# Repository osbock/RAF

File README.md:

# RAF - Ready...Aim...Fire!
Software for a beginning programming class with Arduino, and IOT programming with MQTT. Hardware consists of an Arduino, Shield, Pan/tilt mechanism and pneumatic components for firing foam darts

## Instructions
 * [Assembly Instructions](./Documents/Assembly.md)
 * [Software setup](./Documents/Software.md)

## Software requirements
 * Arduino IDE
 * Python 3.X
 * Adafruit IOT python package

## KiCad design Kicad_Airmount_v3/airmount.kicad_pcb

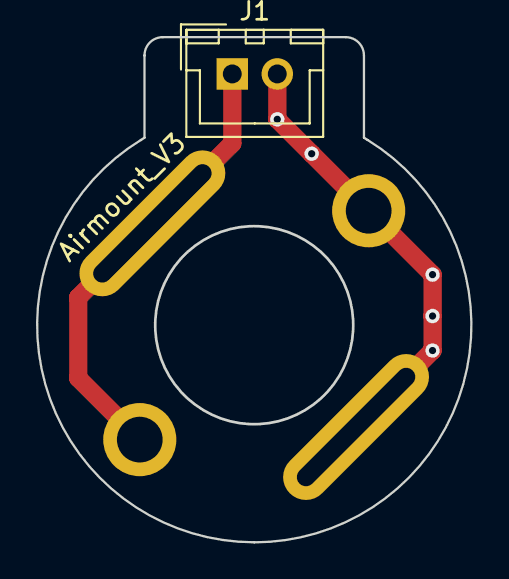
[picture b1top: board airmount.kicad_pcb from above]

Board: 2 copper layers, 24.1 x 28.0 mm, 4 parts (0 on the bottom side), 2 nets.

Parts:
Board1: pumpBoard2
J1: JST; JST_XH_B02B-XH-A_02x2.50mm_Straight
M1: Motor_DC; p_contacts2
M2: Motor_DC; GasSolenoid2

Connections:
GND: J1.2, M1.2, M2.2
unnamed: J1.1, M1.1, M2.1

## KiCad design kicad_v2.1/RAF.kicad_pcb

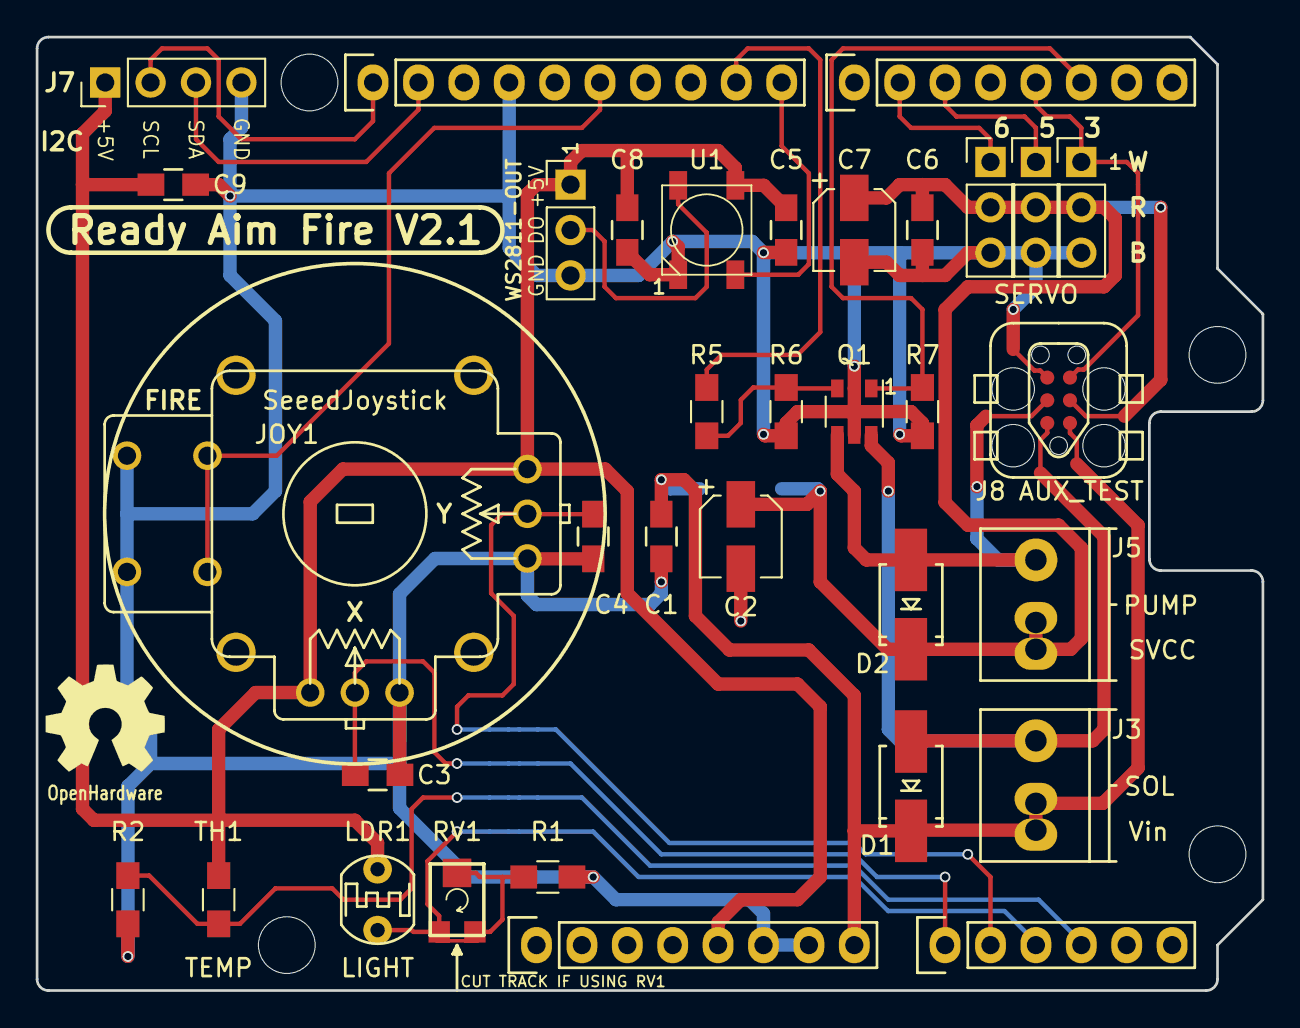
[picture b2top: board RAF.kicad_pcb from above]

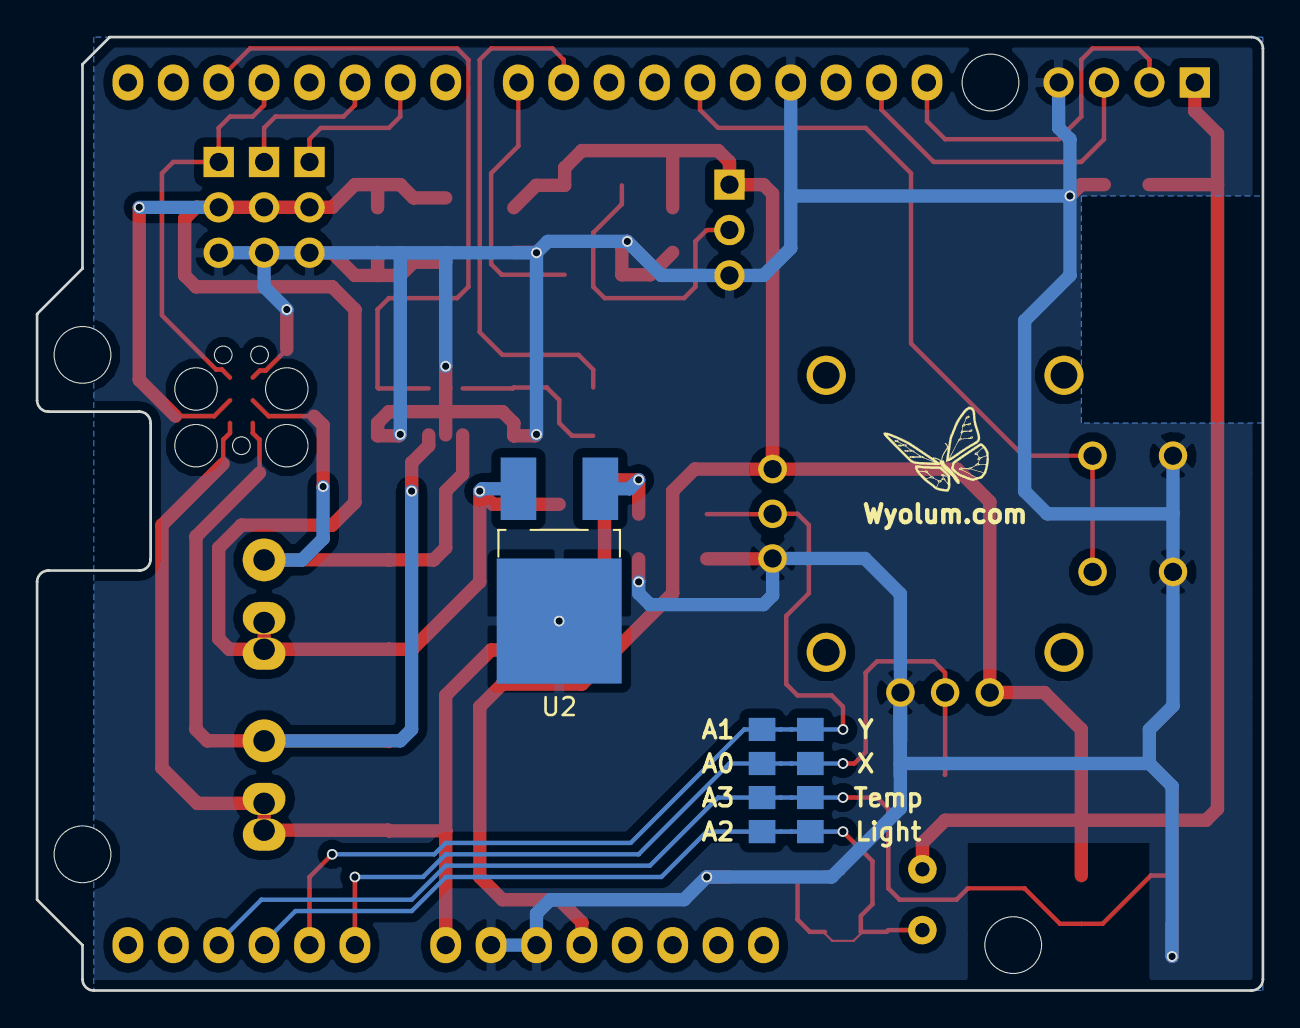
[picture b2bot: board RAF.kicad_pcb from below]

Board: 2 copper layers, 68.6 x 53.3 mm, 45 parts (6 on the bottom side), 21 nets.

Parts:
C1, C3, C4, C5, C6, C8, C9: 0.1uF; C_0805_HandSoldering
C2, C7: 22uF; CP_Elec_4x5.7
D1, D2: S1ATR; SMA_Handsoldering
H1, H2, H3, H4: NPTH_hole; NPTH_hole_3mm
J1, J2, J4: SERVO; Pin_Header_Straight_1x03_Pitch2.54mm
J3: SOL; TerminalBlock_Pheonix_PT-5.0mm_2pol
J5: PUMP; TerminalBlock_Pheonix_PT-5.0mm_2pol
J6: WS2811-OUT; Pin_Header_Straight_1x03_Pitch2.54mm
J7: I2C; Pin_Header_Straight_1x04_Pitch2.54mm
J8: AUX_TEST; TC2030-IDC
JOY1: SeeedJoystick; SEEED-Joystick_v2
JP1, JP2, JP3, JP4: Jumper_NC_Small; 0805_jumper
LDR1: LIGHT; Resistor_LDR_5.0x3.4
OSHW1: OSHW; OSHW_6mm
P1: Power; Socket_Strip_Arduino_1x08
P2: Analog; Socket_Strip_Arduino_1x06
P3: Digital; Socket_Strip_Arduino_1x10
P4: Digital; Socket_Strip_Arduino_1x08
Q1: FDC6305N; SuperSOT-6
R1: 22K; R_0805_HandSoldering
R2: 10K; R_0805_HandSoldering
R5, R6, R7: 100k; R_0805_HandSoldering
RV1: 100k; Res_variable
TH1: TEMP; R_0805_HandSoldering
U1: RGB_WS2811B; LED_WS2812B-PLCC4
U2: LF60CDT; DPak
WYO1: LOGO_WL; logo_wyo_butterfly_small

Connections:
+5V: C5.1, C8.1, C9.1, J6.1, J7.1, JOY1.X+, JOY1.Y+, LDR1.1, P1.5, TH1.1, U1.1
/2: P4.6, Q1.1, R7.2
/3(**): J1.1, J8.5, P4.5
/5(**): J2.1, P4.3
/6(**): J4.1, P4.2
/8: P3.10, U1.4
/9(**): P3.9, R5.2
/12(MISO): JOY1.B1, JOY1.B2, P3.6
/A0: C3.1, JOY1.X, JP1.1, JP1.2, P2.1
/A1: C4.1, JOY1.Y, JP2.1, JP2.2, P2.2
/A2: JP3.1, JP3.2, LDR1.2, P2.3, R1.1, RV1.1, RV1.2, RV1.3
/A3: JP4.1, JP4.2, P2.4, R2.1, TH1.2
/A4(SDA): J7.3, P3.2
/A5(SCL): J7.2, P3.1
/LED_OUT: J6.2, U1.2
/PUMP: D2.2, J5.2, J8.4, Q1.4
/SOL: D1.2, J3.2, J8.2, Q1.6
/SVCC: C2.1, C6.1, C7.1, D2.1, J1.2, J2.2, J4.2, J5.1, J8.3, U2.VO
/Vin: C1.1, D1.1, J3.1, J8.1, P1.8, U2.VI
GND: C1.2, C2.2, C3.2, C4.2, C5.2, C6.2, C7.2, C8.2, C9.2, J1.3, J2.3, J4.3, J6.3, J7.4, J8.6, JOY1.A1, JOY1.A2, JOY1.X-, JOY1.Y-, P1.6, P1.7, P3.4, Q1.2, Q1.5, R1.2, R2.2, R6.1, R7.1, U1.3, U2.GND
unnamed: Q1.3, R5.1, R6.2

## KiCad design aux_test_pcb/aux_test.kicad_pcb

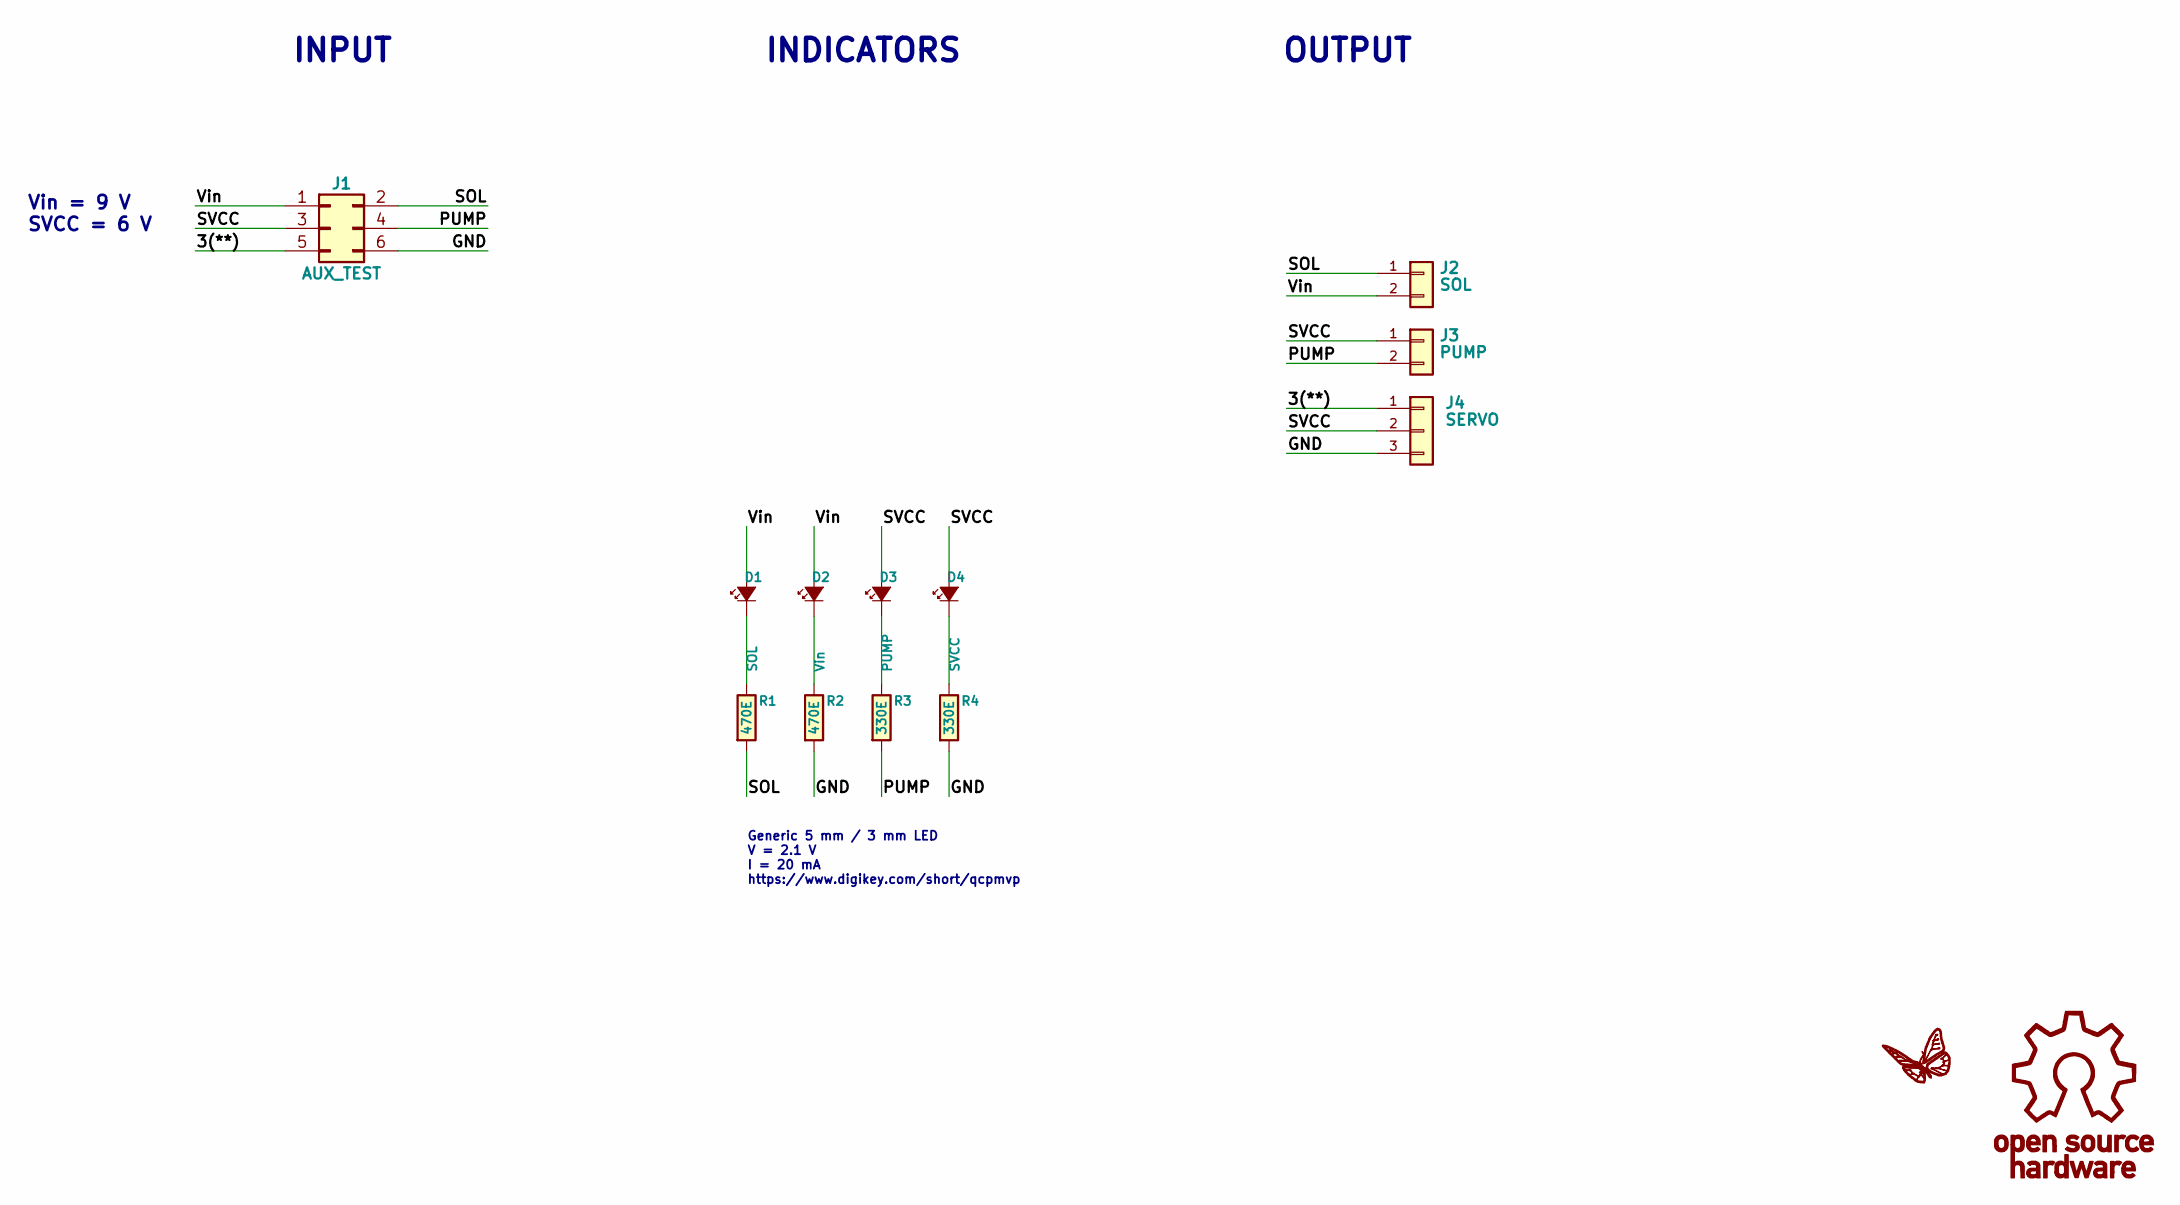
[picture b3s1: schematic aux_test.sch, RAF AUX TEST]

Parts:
D1: SOL; LED-5MM
D2: Vin; LED-5MM
D3: PUMP; LED-5MM
D4: SVCC; LED-5MM
J1: AUX_TEST; Pin_Header_Straight_2x03
J2: SOL; TerminalBlock_Pheonix_PT-5.0mm_2pol
J3: PUMP; TerminalBlock_Pheonix_PT-5.0mm_2pol
J4: SERVO; Pin_Header_Straight_1x03_Pitch2.54mm
R1, R2: 470E; Resistor_Horizontal_RM10mm
R3, R4: 330E; Resistor_Horizontal_RM10mm

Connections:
/3(**): J1.5, J4.1
/GND: J1.6, J4.3, R2.2, R4.2
/PUMP: J1.4, J3.2, R3.2
/SOL: J1.2, J2.1, R1.2
/SVCC: D3.1 (A), D4.1 (A), J1.3, J3.1, J4.2
/Vin: D1.1 (A), D2.1 (A), J1.1, J2.2
unnamed: D1.2 (K), R1.1
unnamed: D2.2 (K), R2.1
unnamed: D3.2 (K), R3.1
unnamed: D4.2 (K), R4.1

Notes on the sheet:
Generic 5 mm / 3 mm LED V = 2.1 V I = 20 mA https://www.digikey.com/short/qcpmvp
INPUT
INDICATORS
OUTPUT
Vin = 9 V SVCC = 6 V

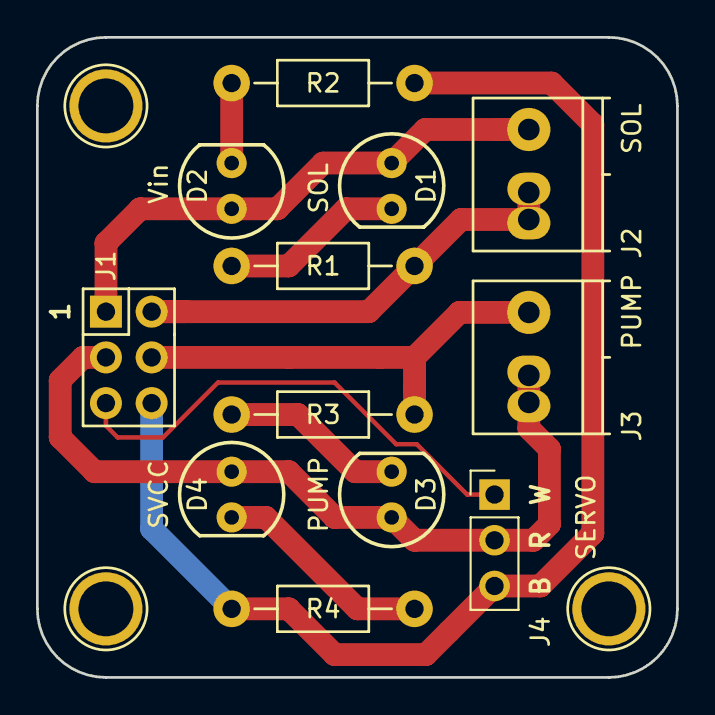
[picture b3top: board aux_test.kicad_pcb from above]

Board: 2 copper layers, 35.6 x 35.6 mm, 15 parts (0 on the bottom side), 10 nets.

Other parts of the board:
1pin, 1pin#2, 1pin#3: VAL**; hole_3mm

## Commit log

2017-05-15 Add arduino code
2017-05-15 add readme
2017-05-15 add documentation
2017-05-15 start python mqtt proxy
2017-05-16 add serial version, adjust servo senters for new pantilt
2017-05-16 update for azimuth/elevation and fire feeds:
2017-05-17 add software setup instructions
2017-05-17 cross link software in README
2017-05-17 fix header
2017-05-17 add fire command to rafserial
2017-05-17 fix fire func in rafserial, limits
2017-05-19 add mounting plate
2017-05-22 add legs, move holes around a bit
2017-07-07 new cloud service [wip]
2017-07-13 update servo positions
2017-07-13 servo align sketch for pan tilt assembly
2017-07-24 initial commit, kicad version Ready Aim Fire Shield V2
2017-07-25 mostly finished schematic
2017-07-25 add sot23-6 footprint, fix drc errors
2017-07-25 add i2c header
2017-07-25 update footprint allocation
2017-08-01 new parts, initial layout, backup of switcher design
2017-08-02 layout and gerbers
2017-08-09 add RAF2 Example
2017-08-09 add pin 1 indications for LED and mosfet
2017-08-09 add FastLED copy, update RAF2 example
2017-08-11 add FastLED support
2017-08-22 add seeed bom
2017-08-23 updated do not populate
2017-08-23 add labels for the mosfet terminals
2017-08-24 HW ver2 of kicad
2017-08-24 RAF v3 Kicad WIP
2017-08-25 add pcb spec file for Seeed
2017-08-25 RAF v2.1 kicad layout
2017-08-25 folder rename
2017-08-25 update bom for cds and datasheet
2017-08-25 LDR footprint modified
2017-08-25 removed kicad_v2 folder
2017-08-26 PCB ver2.1 complete, added variable resistor for LDR
2017-08-26 kicad_v2.1 updated silkscreen
2017-08-26 added FreeCad and step models of PCB to fabricate folder
2017-09-05 add seeed joystick info
2017-09-05 seeed joystick revision
2017-09-05 joystick 3D updated
2017-09-05 updated 3D model in fabricate
2017-09-06 added pogo connector for testing solenoid, pump, servo
2017-09-06 cleaned up silk legend
2017-09-07 aux_text board for production testing
2017-09-08 aux_test minor mods
2017-09-18 fix C2 and C7 value, update to 5mm screw terminals
2017-09-20 pin 1 markers added on silk legend
2017-09-20 updated images
2017-09-21 fix servo legend
2017-09-21 fixed errors in aux_test layout
2017-09-22 updated aux_test PCB
2017-09-22 added aux_test gerber
2017-09-22 refine RAFTest to manufacturing test
2017-10-02 update bom with links
2017-10-03 modified screw terminal solder pads
2017-10-06 remove tactile switch
2017-10-09 edited values of C2,C7
2017-10-12 cleanup
2017-12-15 update for new pan/tilt
2017-12-20 add missing 3d printed pieces
2017-12-22 add assembly v2 images
2017-12-22 update for v2 and air pump
2018-01-02 update content image
2018-01-02 rotate some images:
2018-01-02 New V2 assembly instructions (incomplete)
2018-01-02 finished through Pneumatic assembly.
2018-01-02 rotate another image
2018-01-02 incremental update to assembly instructions
2018-01-02 Link in assembly instrcutions
2018-01-02 and done with Assembly.md
2018-01-02 crop overview pic
2018-01-03 add formatted assembly instructions
2018-01-09 update bom
2018-04-20 add note about python on macs
2018-04-20 refresh install changes, remove stale downloads
2018-04-20 add ada.io section
2018-05-22 servo-step1
2018-05-22 update raf2 for new servos
2018-06-06 add barrelholder, update solenoid holder
2018-07-27 add airmount pcb
2018-07-28 Airmount _v2 and _v3
2018-07-28 Airmount _v2 and _v3 revised gerbers
2019-04-14 Add slew-not-absolute version
2019-04-14 Autoformat
2019-04-14 remove old RAF code
2019-05-14 Make python setup optional/warning about accuracy
2019-07-22 update readme to make IOT more optional
2019-10-30 Bump werkzeug from 0.12.1 to 0.15.3 in /service
    Bumps [werkzeug](https://github.com/pallets/werkzeug) from 0.12.1 to 0.15.3.
    - [Release notes](https://github.com/pallets/werkzeug/releases)
    - [Changelog](https://github.com/pallets/werkzeug/blob/master/CHANGES.rst)
    - [Commits](https://github.com/pallets/werkzeug/compare/0.12.1...0.15.3)
2020-01-08 Bump python-engineio from 1.5.1 to 3.8.2.post1 in /service
    Bumps [python-engineio](https://github.com/miguelgrinberg/python-engineio) from 1.5.1 to 3.8.2.post1.
    - [Release notes](https://github.com/miguelgrinberg/python-engineio/releases)
    - [Changelog](https://github.com/miguelgrinberg/python-engineio/blob/master/CHANGES.md)
    - [Commits](https://github.com/miguelgrinberg/python-engineio/commits)
2020-01-08 Bump flask from 0.12.1 to 1.0 in /service
    Bumps [flask](https://github.com/pallets/flask) from 0.12.1 to 1.0.
    - [Release notes](https://github.com/pallets/flask/releases)
    - [Changelog](https://github.com/pallets/flask/blob/master/CHANGES.rst)
    - [Commits](https://github.com/pallets/flask/compare/0.12.1...1.0)
2020-01-08 Bump requests from 2.14.2 to 2.20.0 in /service
    Bumps [requests](https://github.com/requests/requests) from 2.14.2 to 2.20.0.
    - [Release notes](https://github.com/requests/requests/releases)
    - [Changelog](https://github.com/psf/requests/blob/master/HISTORY.md)
    - [Commits](https://github.com/requests/requests/compare/v2.14.2...v2.20.0)
2020-01-08 Add instructor materials, move tools into section
2020-01-10 add new assembly photos
2020-01-10 Start inserting new pictures
2020-01-10 mv v3 assembly images
2020-01-10 interim assembly edits
2020-01-27 change picture, remove obsolete bom
2020-04-11 added PAPR_controller
2021-03-19 Bump jinja2 from 2.9.6 to 2.11.3 in /service
    Bumps [jinja2](https://github.com/pallets/jinja) from 2.9.6 to 2.11.3.
    - [Release notes](https://github.com/pallets/jinja/releases)
    - [Changelog](https://github.com/pallets/jinja/blob/master/CHANGES.rst)
    - [Commits](https://github.com/pallets/jinja/compare/2.9.6...2.11.3)
